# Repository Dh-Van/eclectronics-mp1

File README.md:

# ENGR 3430 Miniproject 1 – USB LED Flasher

A USB-stick style board that plugs into a USB-A port, regulates 5 V down to 3.3 V, and blinks a red LED with a 1 s period using an op-amp relaxation oscillator.

## Folder layout

| Folder | What's in it |
|---|---|
| `kicad/` | KiCad 10 project: schematic, PCB layout, project settings. `kicad/lib/` holds the custom symbol library (`Eclectronics.kicad_sym`) and footprints (`Eclectronics.pretty/`) for the USB plug, MCP1702 and MCP6021. The project's `sym-lib-table` / `fp-lib-table` point at these with `${KIPRJMOD}` paths, so the project opens on any machine with no extra setup. |
| `ltspice/` | LTspice simulation. `sim.asc` is the 500-run Monte Carlo of the oscillator period (1 % resistors, 5 % cap); `sim.log` has the measured period for every run. The 290 MB `sim.raw` waveform file is not committed – rerun `sim.asc` to regenerate it. |
| `docs/` | `MP1_report.md` / `MP1_report.pdf` (design choices + period analysis; `build_pdf.py` regenerates the PDF with lualatex), `MP1_BOM.csv`, `MP1_schematic.pdf`, the assignment PDF and the allowed parts list. |

## Key numbers

- Period: 1.000 s by hand calculation, 0.987 s mean in simulation, worst case -6.8 % / +7.1 % (spec is +/-10 %).
- Board: 2 layers, 16.1 mm x 14.0 mm, all parts on top, back side is a ground pour. DRC clean.

## Opening the project

Open `kicad/MP1.kicad_pro` in KiCad 10. Note: the LTspice sim names differ from the KiCad schematic (sim R4 = KiCad R5, sim R5 = KiCad R4, sim C1 = KiCad C4); see the report.

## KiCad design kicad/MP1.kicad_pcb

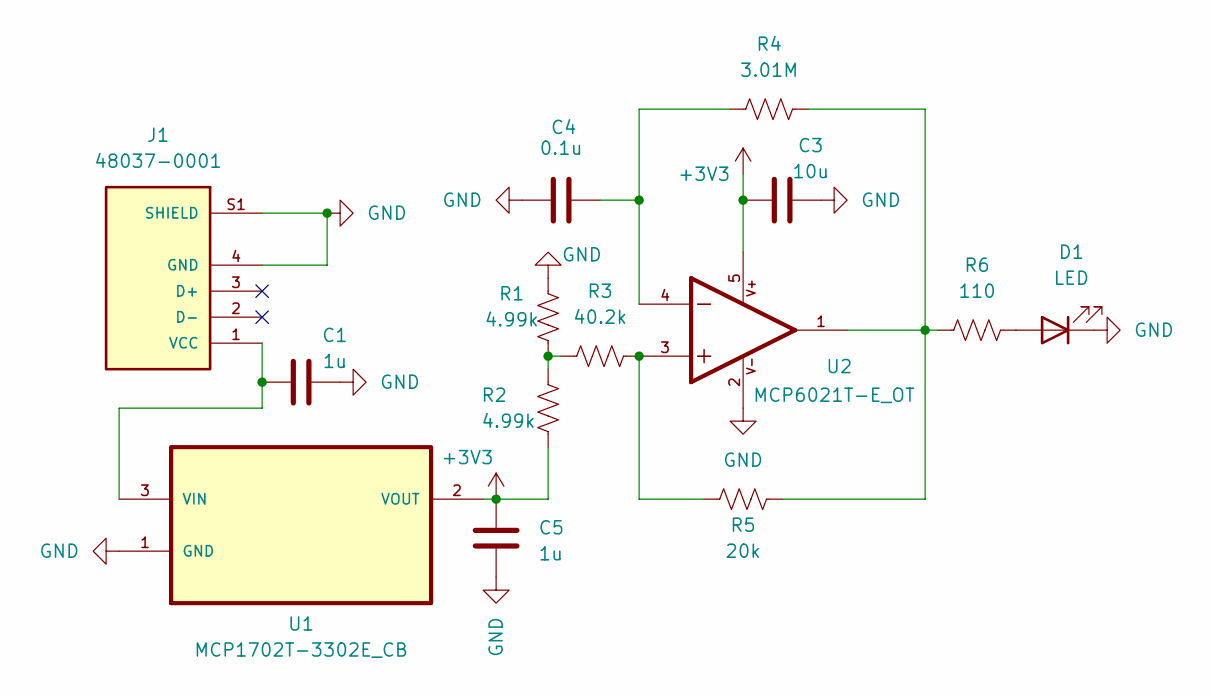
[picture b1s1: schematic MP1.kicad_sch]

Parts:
C1, C5: 1u; C_0603_1608Metric
C3: 10u; C_0603_1608Metric
C4: 0.1u; C_0603_1608Metric
D1: LED; LED_0805_2012Metric
J1: 48037-0001; MOLEX_48037-0001; PARTREV D
R1, R2: 4.99k; R_0603_1608Metric
R3: 40.2k; R_0603_1608Metric
R4: 3.01M; R_0603_1608Metric
R5: 20k; R_0603_1608Metric
R6: 110; R_0603_1608Metric
U1: MCP1702T-3302E_CB; SOT95P255X145-3N; MPN MCP1702T-3302E/CB; DigiKey_Part_Number MCP1702T-3302E/CBCT-ND
U2: MCP6021T-E_OT; SOT95P280X145-5N; PARTREV E

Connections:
+3V3: C3.1, C5.1, R2.2, U1.2 (VOUT), U2.5
GND: C1.2, C3.2, C4.1, C5.2, D1.1 (K), J1.4 (GND), J1.S1 (SHIELD), J1.S2 (SHIELD), R1.1, U1.1 (GND), U2.2
unnamed: C4.2, R4.1, U2.4
unnamed: D1.2 (A), R6.2
unnamed: C1.1, J1.1 (VCC), U1.3 (VIN)
unnamed: R1.2, R2.1, R3.1
unnamed: R3.2, R5.1, U2.3
unnamed: R4.2, R5.2, R6.1, U2.1

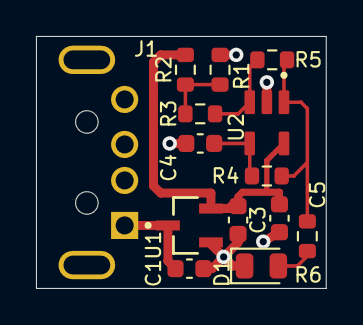
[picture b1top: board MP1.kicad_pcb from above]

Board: 2 copper layers, 16.1 x 14.0 mm, 14 parts (0 on the bottom side), 8 nets.
